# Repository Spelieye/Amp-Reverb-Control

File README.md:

# Amp-Reverb-Control
Ever wish that you could control your amplifier's reverb effect on the fly without major modification to your amplifier? Well now your wish can become a reality! 

This is a reverb control platform that can be placed into an amplifier and has a remote pedal that controls the reverb effect. 

It has two parts: the master mcu unit that goes into the amplifier and a slave mcu unit in a pedal. You replace the reverb pot in the amplifier with the digital one on the PCB so the audio signal stays inside of the amplifier. The existing reverb pot -- if it is a 100kA pot-- connects to the master mcu board to control the reverb locally if the pedal is not plugged in. 
Connect the master mcu to the pedal mcu via a 6 pin GX12 cable and you are now able to remotely control the reverb. You can select between two different levels and turn the effect on or off. 

## The Build

The mcu on both boards is an Atmel ATtiny26L. The PCB boards were designed to be easy to install into an amplifier and a pedal. 

### AMP PCB

### Pedal PCB 

### Pedal Assembly

### Full photo of the master mcu installed in the amp

### Close up of the master MCU showing the audio signal path. Red is input to the digital pot and blue is output of the digital pot. 

### Real pics of pedal

## Schematic for connecting the master MCU 

### Signal Connection

### Power Connection

The 6 pin comms header connects to "Slave_MCU" header on both boards. 

## Flashing 

To flash the mcus be sure to use the correct `.hex` file for the associated board. Connect your flasher to the ISP header. 

First update the fuses

```
avrdude -c usbtiny -p t26 -U lfuse:w:0xc4:m -U hfuse:w:0xf6:m
```

Flashing the master board
```
avrdude -c usbtiny -p t26 -U flash:w:amp_master_rev1.hex
```

Flashing the pedal board 
```
avrdude -c usbtiny -p t26 -U flash:w:pedal_slave_rev1.hex
```
## Video of Pedal Demo

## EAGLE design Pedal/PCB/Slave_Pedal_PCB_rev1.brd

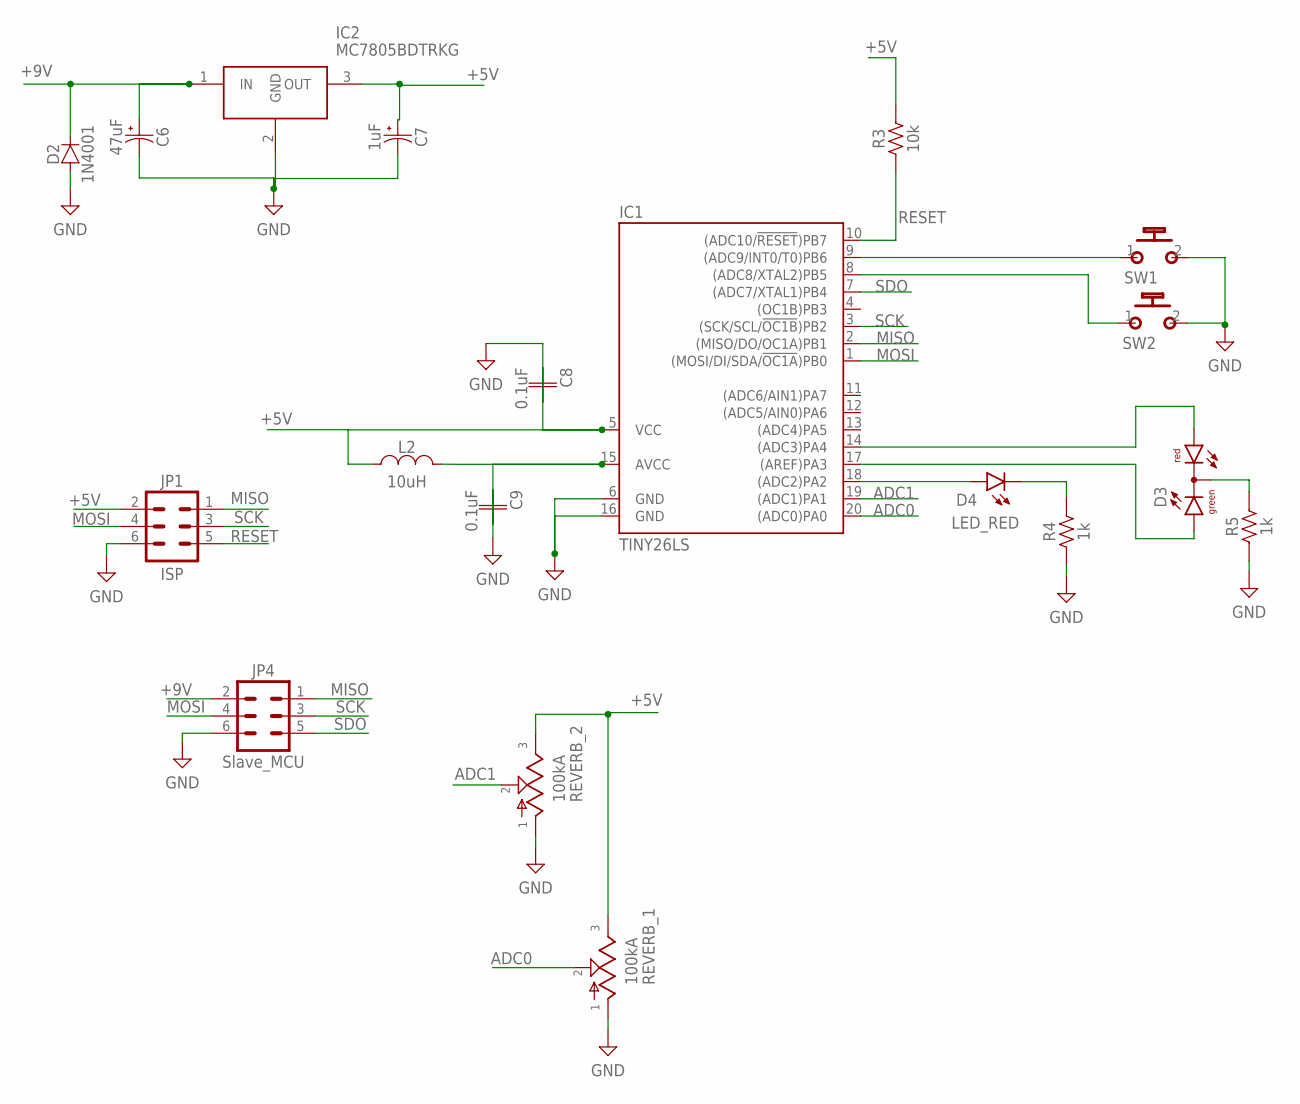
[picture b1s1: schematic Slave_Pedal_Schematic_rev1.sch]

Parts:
C6: 47uF; CAPAE430X430N
C7: 1uF; CAPAE430X430N
C8, C9: 0.1uF; CAPC3216X135
D2: 1N4001; DIOM5226X290N
D3: DUOLED5MMRGLED_LIFTED; DUOLED-C-5MM
D4: LED_RED; LEDRD254W60D565H860B
IC1: TINY26LS; SO20L
IC2: MC7805BDTRKG; LM317MADTRKG
JP1: ISP; 2X3-SHROUDED
JP4: Slave_MCU; 2X3-SHROUDED
L2: 10uH; INDC3216X190
R3: 10k; RESC3216X70
R4, R5: 1k; RESC3216X70
REVERB_1, REVERB_2: 100kA; 16MM
SW1, SW2: MOMENTARYJST; B2B-XH-A

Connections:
+5V: C7.1 (+), C8.1, IC1.5 (VCC), IC2.3 (OUT), JP1.2, L2.1, R3.2, REVERB_1.3, REVERB_2.3
+9V: C6.1 (+), D2.1 (C), IC2.1 (IN), JP4.2
ADC0: IC1.20 ((ADC0)PA0), REVERB_1.2
ADC1: IC1.19 ((ADC1)PA1), REVERB_2.2
GND: C6.2 (-), C7.2 (-), C8.2, C9.1, D2.2 (A), IC1.6 (GND), IC1.16 (GND), IC2.2 (GND), JP1.6, JP4.6, R4.1, R5.1, REVERB_1.1, REVERB_2.1, SW1.2 (S), SW2.2 (S)
MISO: IC1.2 ((MISO/DO/OC1A)PB1), JP1.1, JP4.1
MOSI: IC1.1 ((MOSI/DI/SDA/!OC1A!)PB0), JP1.4, JP4.4
unnamed: IC1.9 ((ADC9/INT0/T0)PB6), SW1.1
unnamed: IC1.8 ((ADC8/XTAL2)PB5), SW2.1
unnamed: D3.AR, IC1.14 ((ADC3)PA4)
unnamed: D4.1 (A), IC1.18 ((ADC2)PA2)
unnamed: D3.AX (AG), IC1.17 ((AREF)PA3)
unnamed: C9.2, IC1.15 (AVCC), L2.2
unnamed: D4.2 (C), R4.2
unnamed: D3.C, R5.2
RESET: IC1.10 ((ADC10/!RESET!)PB7), JP1.5, R3.1
SCK: IC1.3 ((SCK/SCL/!OC1B!)PB2), JP1.3, JP4.3
SDO: IC1.7 ((ADC7/XTAL1)PB4), JP4.5

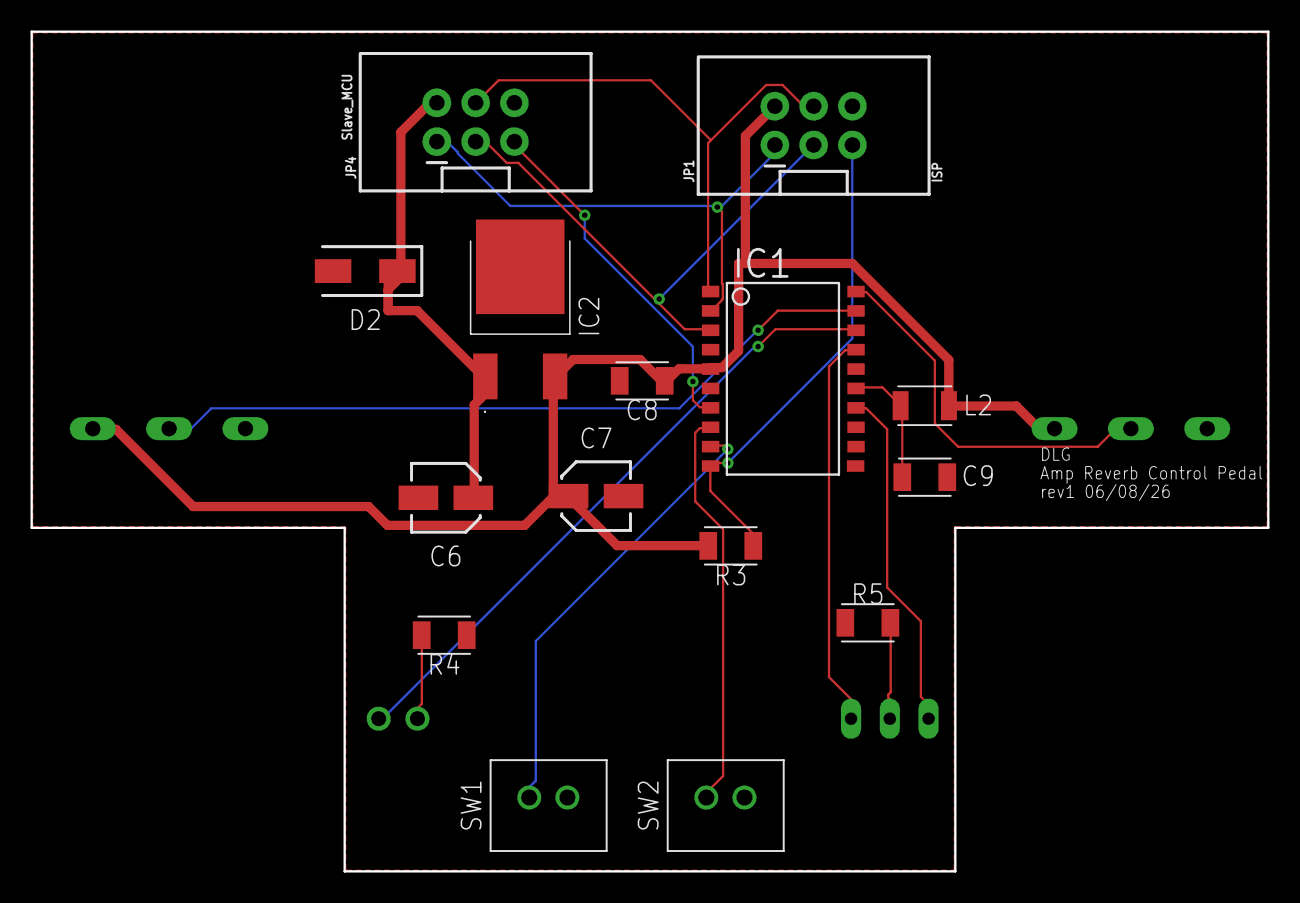
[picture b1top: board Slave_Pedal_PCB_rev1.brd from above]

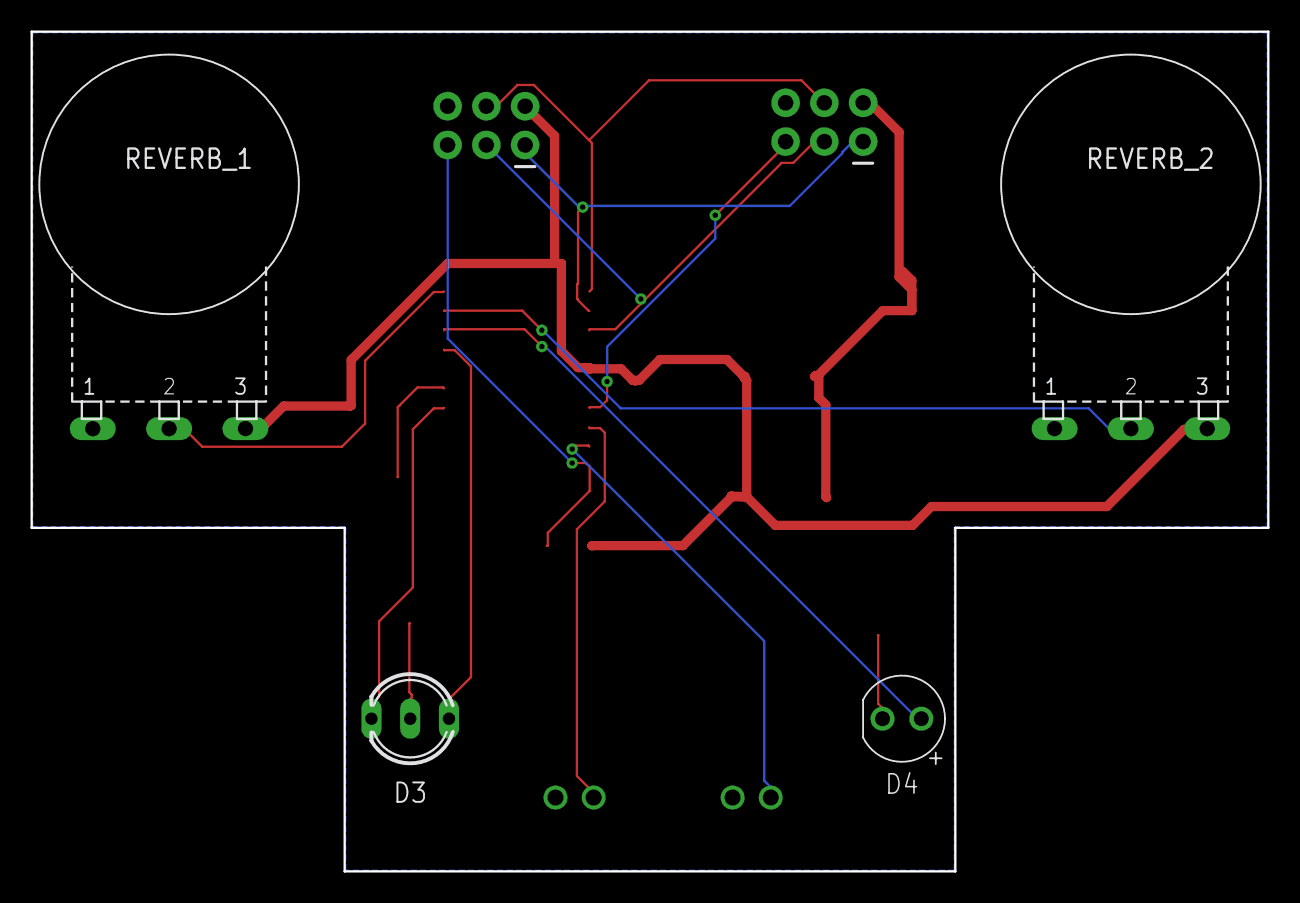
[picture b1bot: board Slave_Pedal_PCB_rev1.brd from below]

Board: 2 copper layers, 81.0 x 55.0 mm, 19 parts (4 on the bottom side), 18 nets.

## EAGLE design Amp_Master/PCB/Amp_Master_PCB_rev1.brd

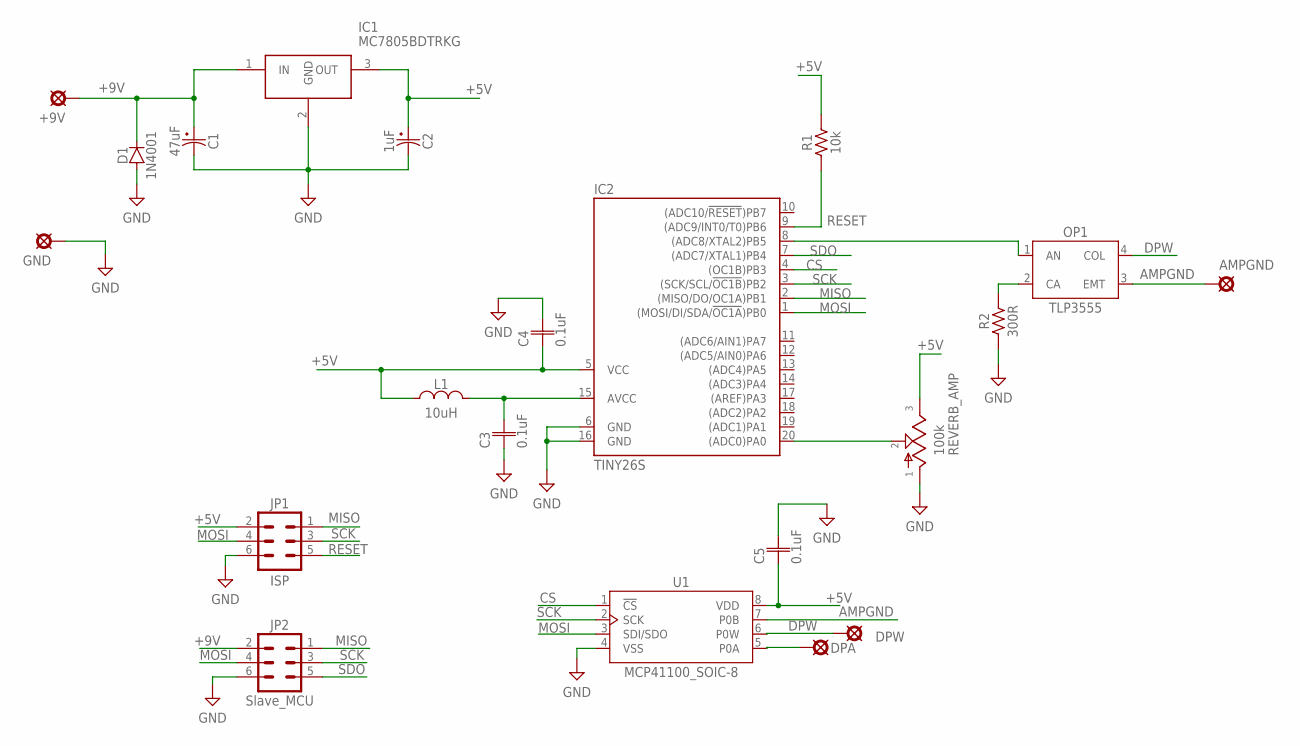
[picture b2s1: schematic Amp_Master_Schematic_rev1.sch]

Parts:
+9V: PADSQUARE_20AWG; SQUARE_0.813MM
AMPGND: PADSQUARE_20AWG; SQUARE_0.813MM
C1: 47uF; CAPAE430X430N
C2: 1uF; CAPAE430X430N
C3, C4, C5: 0.1uF; CAPC3216X135
D1: 1N4001; DIOM5226X290N
DPA: PADSQUARE_20AWG; SQUARE_0.813MM
DPW: PADSQUARE_20AWG; SQUARE_0.813MM
GND: PADSQUARE_20AWG; SQUARE_0.813MM
IC1: MC7805BDTRKG; LM317MADTRKG
IC2: TINY26S; SO20L
JP1: ISP; 2X3-SHROUDED
JP2: Slave_MCU; 2X3-SHROUDED
L1: 10uH; INDC3216X190
OP1: TLP3555; DIP4
R1: 10k; RESC3216X70
R2: 300R; RESC3216X70
REVERB_AMP: 100k; 16MM-PCB-MOUNT
U1: MCP41100_SOIC-8; SOIC127P600X175-8N

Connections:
+5V: C2.1 (+), C4.1, C5.1, IC1.3 (OUT), IC2.5 (VCC), JP1.2, L1.1, R1.2, REVERB_AMP.3, U1.8 (VDD)
+5V1: C3.2, IC2.15 (AVCC), L1.2
+9V: +9V.1, C1.1 (+), D1.1 (C), IC1.1 (IN), JP2.2
AMPGND: AMPGND.1, OP1.3 (EMT), U1.7 (P0B)
CS: IC2.4 ((OC1B)PB3), U1.1 (!CS)
DPW: DPW.1, OP1.4 (COL), U1.6 (P0W)
GND: C1.2 (-), C2.2 (-), C3.1, C4.2, C5.2, D1.2 (A), GND.1, IC1.2 (GND), IC2.6 (GND), IC2.16 (GND), JP1.6, JP2.6, R2.1, REVERB_AMP.1, U1.4 (VSS)
MISO: IC2.2 ((MISO/DO/OC1A)PB1), JP1.1, JP2.1
MOSI: IC2.1 ((MOSI/DI/SDA/!OC1A!)PB0), JP1.4, JP2.4, U1.3 (SDI/SDO)
unnamed: IC2.20 ((ADC0)PA0), REVERB_AMP.2
unnamed: IC2.8 ((ADC8/XTAL2)PB5), OP1.1 (AN)
unnamed: OP1.2 (CA), R2.2
unnamed: DPA.1, U1.5 (P0A)
RESET: IC2.9 ((ADC9/INT0/T0)PB6), JP1.5, R1.1
SCK: IC2.3 ((SCK/SCL/!OC1B!)PB2), JP1.3, JP2.3, U1.2 (SCK)
SDO: IC2.7 ((ADC7/XTAL1)PB4), JP2.5

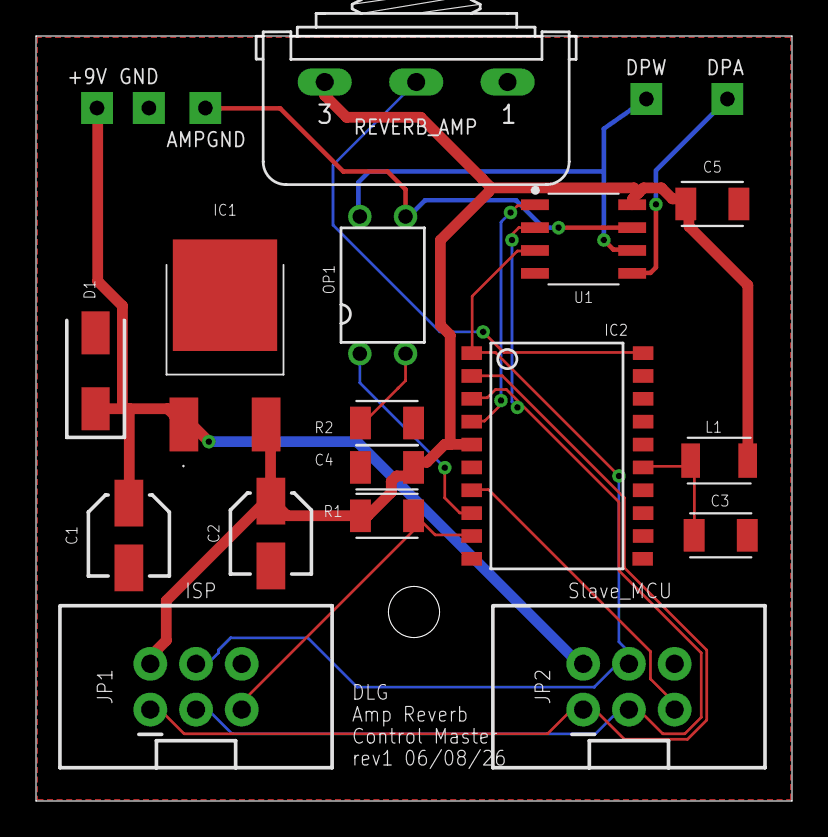
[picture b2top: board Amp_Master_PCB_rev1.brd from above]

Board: 2 copper layers, 42.0 x 42.5 mm, 21 parts (0 on the bottom side), 16 nets.

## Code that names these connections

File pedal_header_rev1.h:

#ifndef SLAVE_PEDAL_H
#define SLAVE_PEDAL_H

#include <avr/io.h>
#include <avr/interrupt.h>
#define F_CPU 8000000UL
#include <util/delay.h>
#include <stdint.h>

/* 
 * Pin Definitions based on the Slave Pedal Schematic 
 */

// LED Outputs (Port A)
// Note: PA3 is also AREF. We must use AVCC as the ADC reference 
// so the output driver on PA3 is not disabled.
#define PORT_LED     PORTA
#define DDR_LED      DDRA
#define PIN_LED      PINA
#define PIN_LED_RED  PA2  // D4 Red LED (On/Off)
#define PIN_LED_RG_G PA3  // D3 RG LED Green (Pot 2 active)
#define PIN_LED_RG_R PA4  // D3 RG LED RED (Pot 1 active)

// USI SPI Pins (Port B)
#define PORT_SPI     PORTB
#define DDR_SPI      DDRB
#define PIN_SPI      PINB
#define PIN_DI       PB0  // USI Data Input
#define PIN_DO       PB1  // USI Data Output
#define PIN_USCK     PB2  // USI Clock
#define PIN_CS       PB4  // Chip Select from Master (Triggering PCINT)

// Switch Pins (Port B)
#define PORT_SW      PORTB
#define DDR_SW       DDRB
#define PIN_SW       PINB
#define PIN_SW1      PB6  // On/Off Switch (Triggers INT0)
#define PIN_SW2      PB5  // Selection Switch (Triggers PCINT)

// Protocol Definitions
#define PACKET_HEADER 0xAA

// Function Prototypes
void io_init(void);
void adc_init(void);
uint8_t adc_read(uint8_t channel);
void usi_init(void);
uint8_t calculate_crc8(uint8_t *data, uint8_t len);

#endif // SLAVE_PEDAL_H

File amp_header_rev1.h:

#ifndef AMP_MASTER_H
#define AMP_MASTER_H

#include <avr/io.h>
#define F_CPU 8000000UL
#include <util/delay.h>
#include <stdint.h>

/* 
 * Pin Definitions based on the Amp Master Schematic 
 */
#define PORT_SPI    PORTB
#define DDR_SPI     DDRB
#define PIN_DI      PB1  // Software SPI Data Input (from Slave DO) 
#define PIN_DO      PB0  // Software SPI Data Output (to Slave DI & MCP SDI)
#define PIN_SCK     PB2  // Software SPI Clock that will be manually pulsed
#define PIN_CS_MCP  PB3  // Chip Select for MCP41100
#define PIN_CS_SLV  PB4  // Chip Select for Slave MCU (Labeled SDO on JP2)
#define PIN_TLP     PB5  // TLP3555 Optorelay Control (AN pin)

// Protocol Definitions
#define PACKET_HEADER    0xAA
#define PAYLOAD_MASK     0x01

// Function Prototypes
void io_init(void);
void spi_init(void);
uint8_t spi_transfer(uint8_t data);
void adc_init(void);
uint8_t adc_read_8bit(void);
void mcp41100_set(uint8_t value);
uint8_t calculate_checksum(uint8_t *data, uint8_t len);

// Define the single-bit transfer sequence as a macro
#define SPI_TRANSFER_BIT \
    if (data & 0x80) { \
        PORT_SPI |= (1 << PIN_DO); \
    } else { \
        PORT_SPI &= ~(1 << PIN_DO); \
    } \
    _delay_us(2); \
    PORT_SPI |= (1 << PIN_SCK); \
    _delay_us(2); \
    received_data <<= 1; \
    if (PINB & (1 << PIN_DI)) { \
        received_data |= 0x01; \
    } \
    data <<= 1; \
    PORT_SPI &= ~(1 << PIN_SCK);

#endif // AMP_MASTER_H

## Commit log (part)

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2026-06-12 adding amp master and pedal slave C code and hex files
2026-06-16 added more IF checks to prevent unecessary and repetative pin/port setting

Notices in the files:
parts and their libraries:
SparkFun-Connectors: Licensing: Creative Commons ShareAlike 4.0 International - https://creativecommons.org/licenses/by-sa/4.0
